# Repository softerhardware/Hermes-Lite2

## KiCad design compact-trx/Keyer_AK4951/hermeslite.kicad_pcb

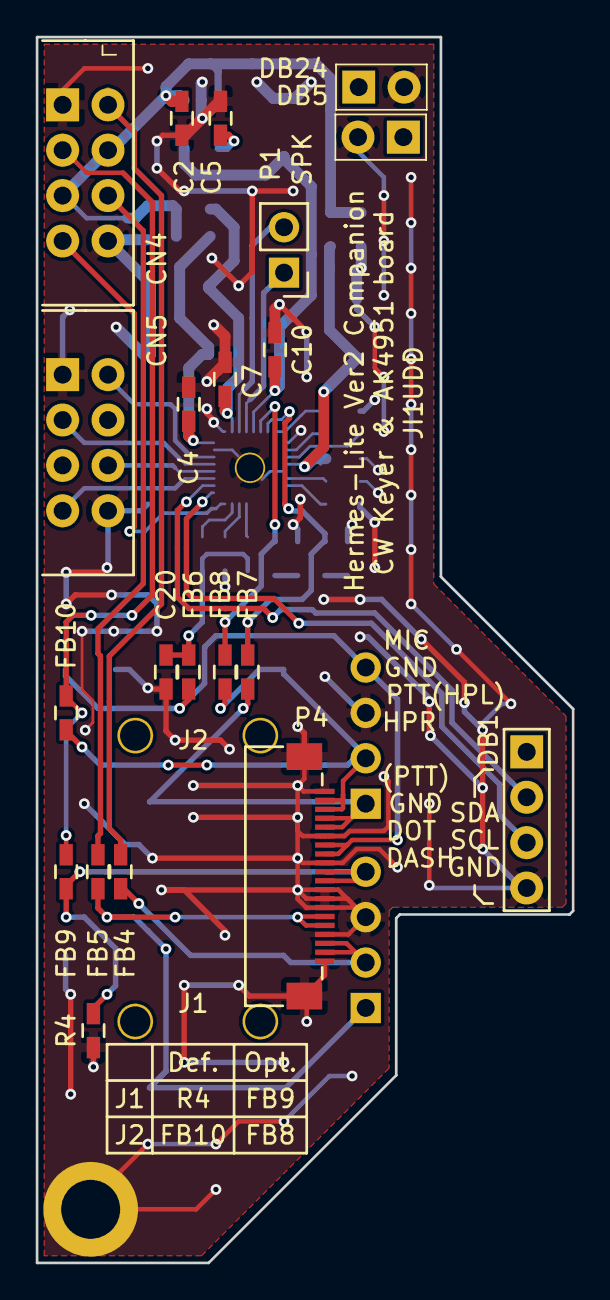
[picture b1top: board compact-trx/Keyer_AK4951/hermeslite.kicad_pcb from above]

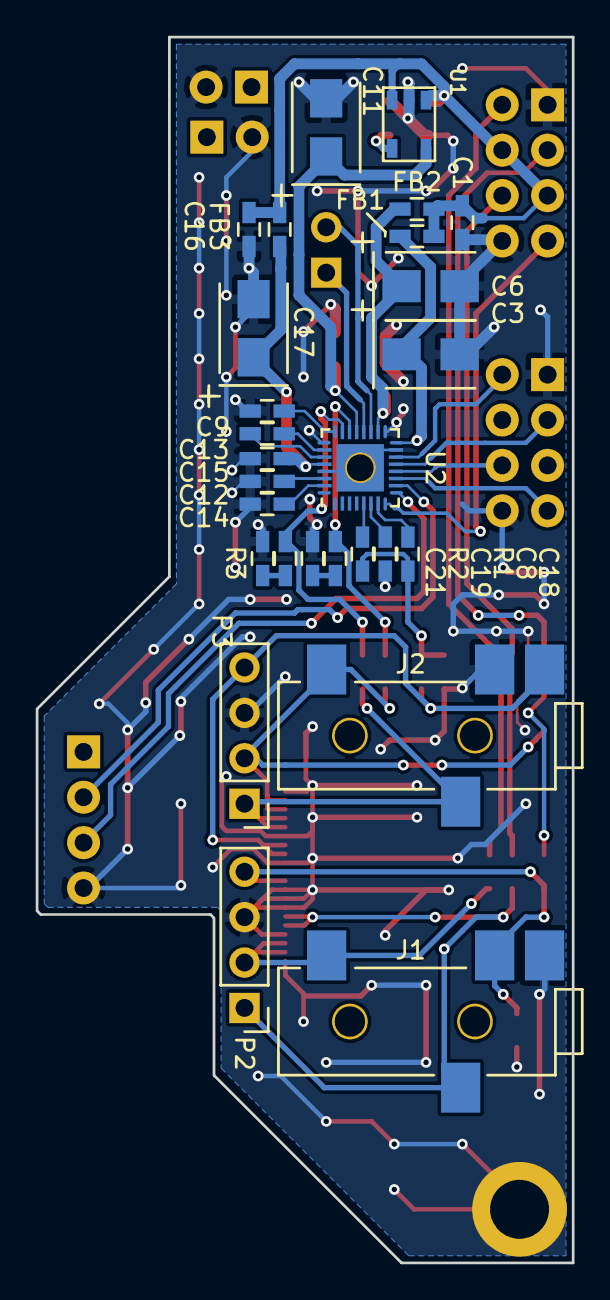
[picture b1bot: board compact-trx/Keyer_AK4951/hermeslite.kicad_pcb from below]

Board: 4 copper layers, 30.0 x 68.6 mm, 49 parts (27 on the bottom side), 38 nets.

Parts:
C1, C4, C5, C7, C10, C15, C16: 0.1u; C_0603_HandSoldering
C2, C8, C18: 1u; C_0603_HandSoldering
C3, C6, C11, C17: 10u; TantalC_SizeB_EIA-3528_Wave
C9, C12, C13, C14: 2.2u; C_0603_HandSoldering
C19, C21: 0.22u; C_0603_HandSoldering
C20: DNI; C_0603_HandSoldering
CN4, CN5: IO8; IO
DB1: RFD4d; 4x1
DB5, DB24: RFD2b; 2x1
FB1, FB2, FB3, FB4, FB5, FB6, FB7, FB8, FB9, FB10: FB; C_0603_HandSoldering
J1, J2: SJ-43514-SMT
MH2: DNI; m3
P1: CONN_01X02; Pin_Header_Straight_1x02_Pitch2.54mm
P2, P3: CONN_01X04; Pin_Header_Straight_1x04_Pitch2.54mm
P4: FFC 20pin; FFC_Kyocera_20pin
R1: 2.2k; C_0603_HandSoldering
R2, R3: 33; C_0603_HandSoldering
R4: 0; C_0603_HandSoldering
U1: TPS730; SOT23
U2: AK4951AEN; QFN-32-1EP_4x4mm_Pitch0.4mm_Handsoldering

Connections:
+3V3: C1.1, C2.1, C16.1, CN4.4, CN4.5, FB1.2, FB2.2, FB3.1, U1.1, U1.3
/AudioCodec/BCK: CN5.2, U2.14
/AudioCodec/DIN: CN5.7, U2.11
/AudioCodec/DOUT: CN5.6, U2.12
/AudioCodec/LRCK: CN5.3, U2.13
/AudioCodec/P2-1: FB5.2, J1.3, P2.1, P4.15, P4.16
/AudioCodec/P2-2: FB4.2, J1.2, P2.2, P4.18, P4.19
/AudioCodec/P2-4: FB9.1, J1.4, P2.4, P4.10, P4.11, R4.2
/AudioCodec/P3-1: FB7.2, J2.3, P3.1, P4.4, P4.5
/AudioCodec/P3-2: FB8.1, FB10.1, J2.2, P3.2, P4.2, P4.3
/AudioCodec/P3-4: FB6.2, J2.1, P3.4, P4.7, P4.8
/AudioCodec/PDN: CN4.7, U2.8
/AudioCodec/SCL: DB1.3, U2.9
/AudioCodec/SDA: DB1.2, U2.10
/AudioCodec/~DASH: CN4.6, FB5.1
/AudioCodec/~DOT: CN4.2, FB4.1
/AudioCodec/~PTT: CN4.3, FB9.2, FB10.2
GND: C1.2, C2.2, C3.2, C4.2, C5.2, C6.2, C7.2, C8.1, C9.2, C10.2, C11.2, C12.2, C14.2, C15.1, C16.2, C17.2, C20.2, CN4.1, CN4.8, CN5.1, CN5.8, DB1.4, DB5.2, DB24.2, J1.1, J2.4, MH2.1, P2.3, P3.3, P4.1, P4.6, P4.9, P4.12, P4.13, P4.14, P4.17, P4.20, P4.21, P4.22, R2.2, R3.2, R4.1, U1.2, U2.15, U2.17, U2.25, U2.29, U2.33
unnamed: C3.1, C4.1, FB1.1, U2.16
unnamed: C5.1, U1.4
unnamed: C6.1, C7.1, FB2.1, U2.18
unnamed: C8.2, U2.6
unnamed: C9.1, U2.24
unnamed: C10.1, C11.1, U1.5, U2.21
unnamed: C12.1, U2.30
unnamed: C13.1, U2.27
unnamed: C13.2, U2.26
unnamed: C14.1, U2.31
unnamed: C15.2, C17.1, FB3.2, U2.28
unnamed: C18.1, U2.7
unnamed: C18.2, C20.1, FB6.1, R1.1
unnamed: C19.1, FB8.2, U2.22
unnamed: C19.2, R2.1
unnamed: C21.1, FB7.1, U2.23
unnamed: C21.2, R3.1
unnamed: P1.1, U2.20
unnamed: P1.2, U2.19
unnamed: R1.2, U2.5

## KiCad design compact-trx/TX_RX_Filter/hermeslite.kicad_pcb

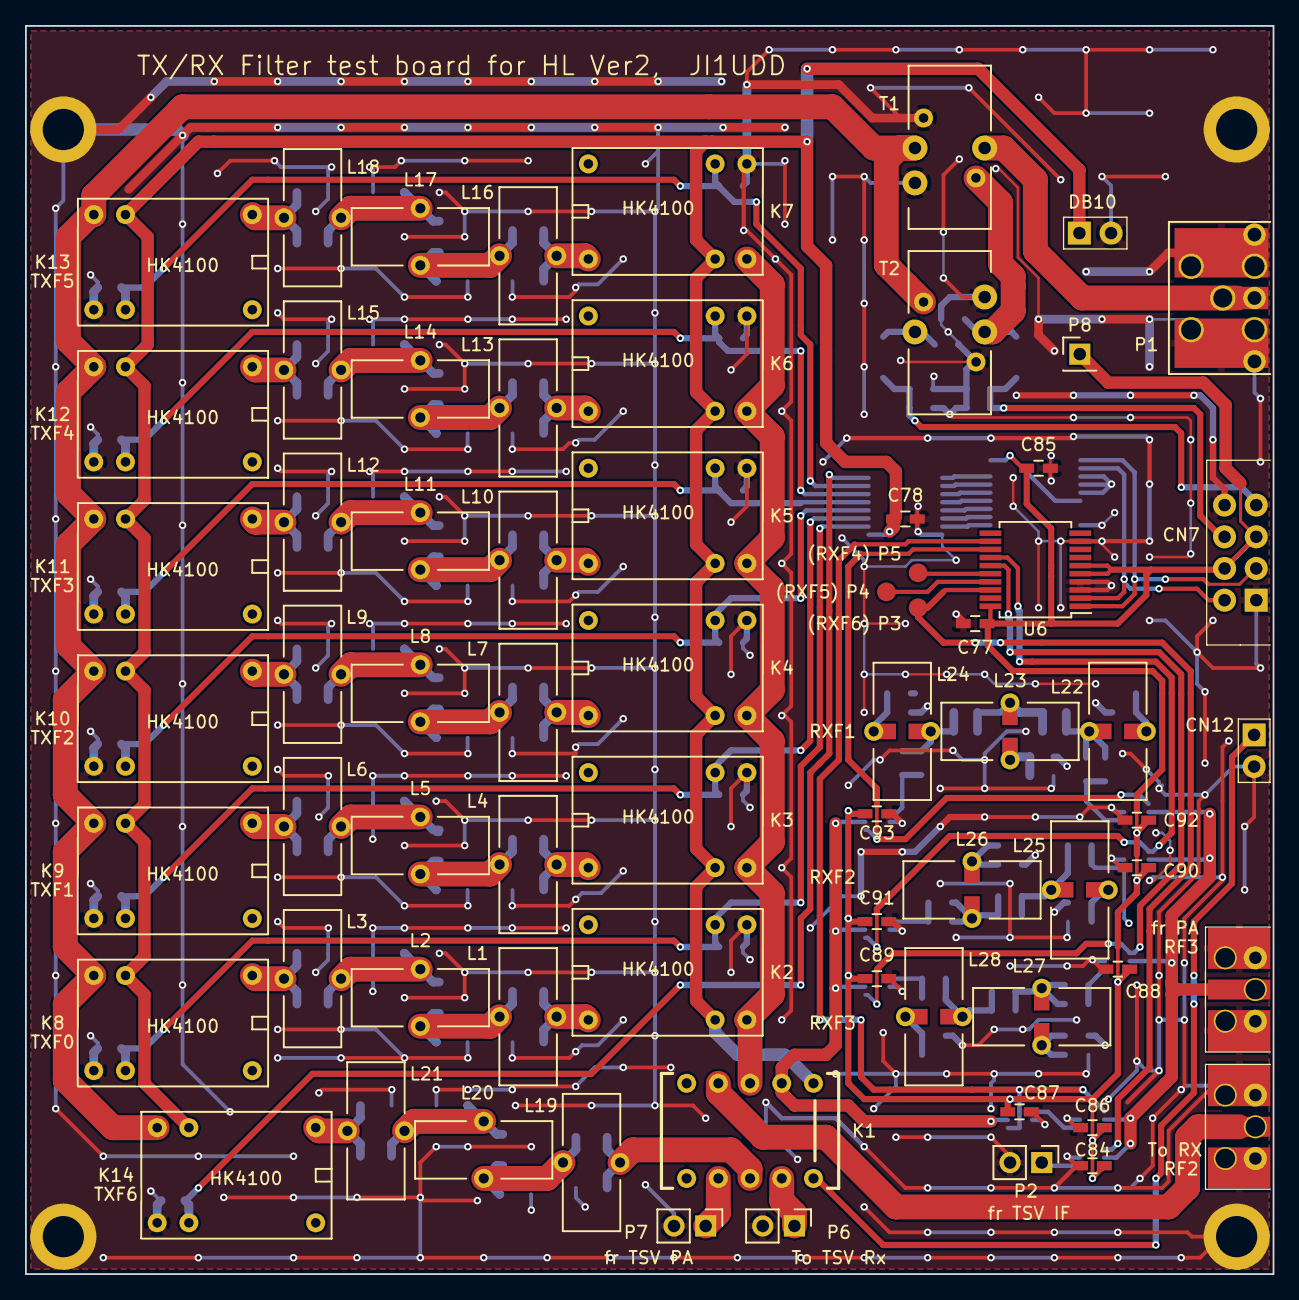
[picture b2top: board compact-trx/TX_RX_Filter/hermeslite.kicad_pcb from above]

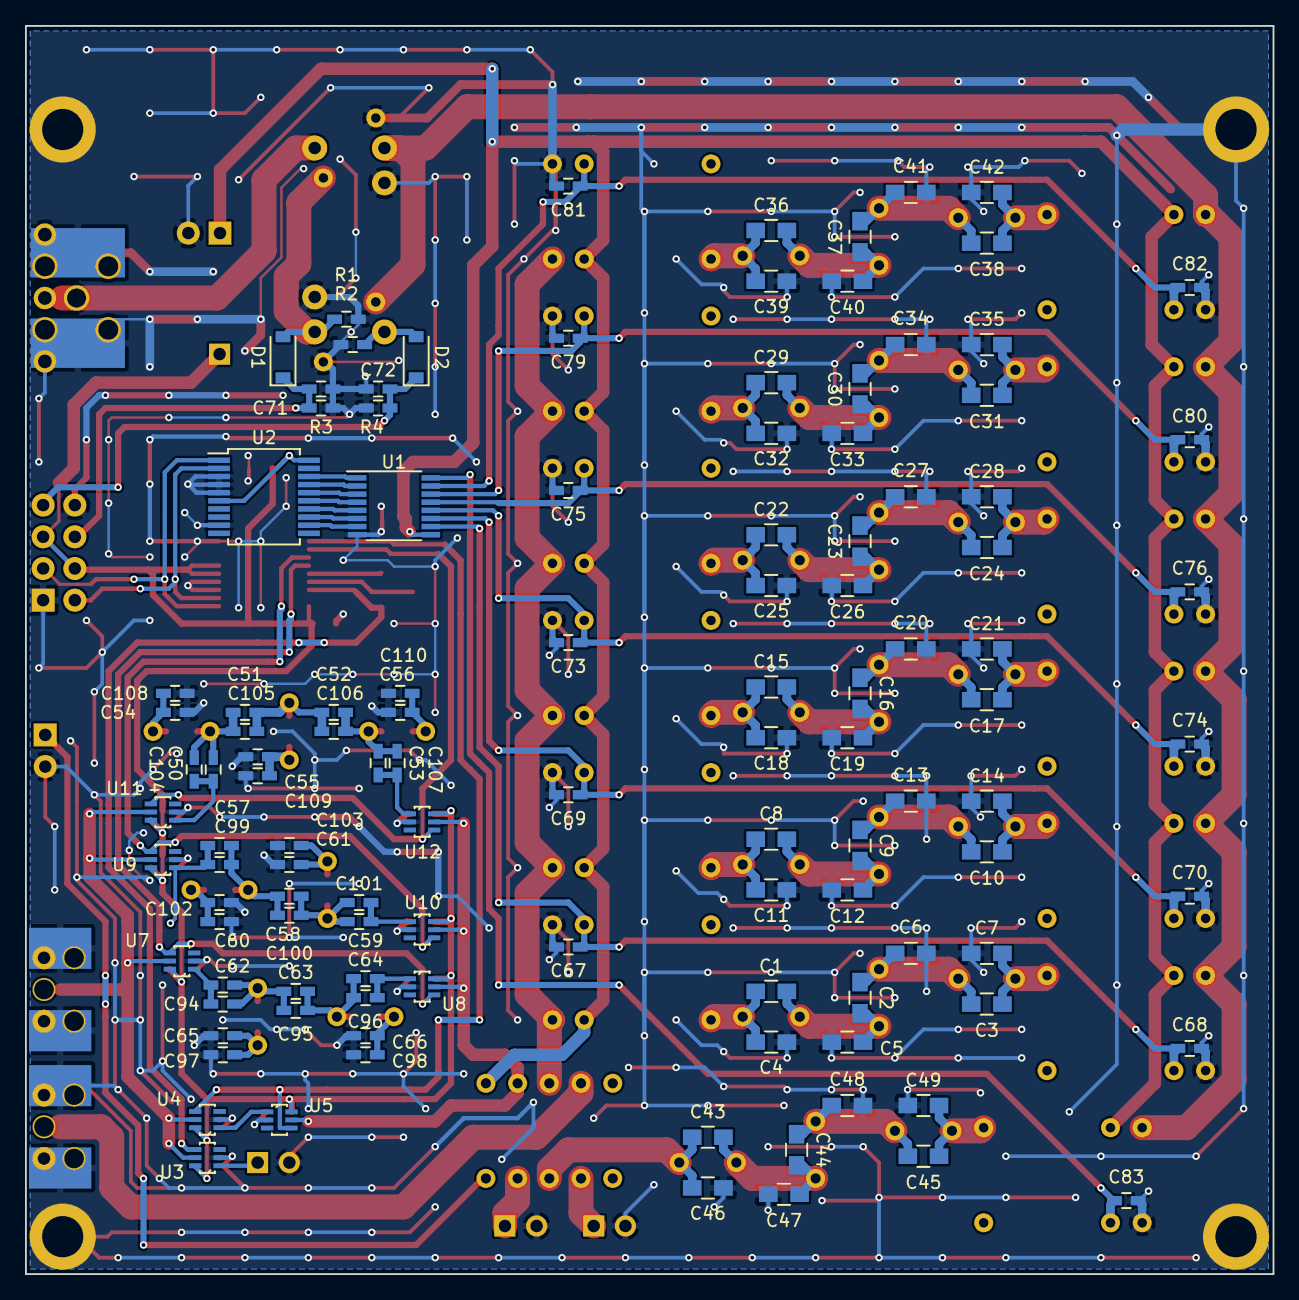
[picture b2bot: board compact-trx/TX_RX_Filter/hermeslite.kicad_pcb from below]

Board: 4 copper layers, 99.9 x 100.0 mm, 189 parts (115 on the bottom side), 89 nets.

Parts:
C1, C2, C3, C8, C9, C10, C17, C28, C29, C30, C31, C36, C37, C38, C43, C44, C45, C46, C47, C48, C49: DNI; C_0805_HandSoldering
C4, C7: 820p; C_0805_HandSoldering
C5, C6: 2200p; C_0805_HandSoldering
C11, C14: 470pF; C_0805_HandSoldering
C12, C13: 1200pF; C_0805_HandSoldering
C15: 100pf; C_0805_HandSoldering
C16: 300pf; C_0805_HandSoldering
C18: 360pF; C_0805_HandSoldering
C19: 680pF; C_0805_HandSoldering
C20: 270pF; C_0805_HandSoldering
C21: 240pF; C_0805_HandSoldering
C22: 43pF; C_0805_HandSoldering
C23, C27: 130pF; C_0805_HandSoldering
C24: 0R Res; C_0805_HandSoldering
C25: 180pF; C_0805_HandSoldering
C26: 300pF; C_0805_HandSoldering
C32, C35: 82pF; C_0805_HandSoldering
C33, C34: 220pF; C_0805_HandSoldering
C39, C42: 100p; C_0805_HandSoldering
C40, C41: 180p; C_0805_HandSoldering
C50, C51, C52, C53, C57, C58, C59, C62, C63, C64, C94, C95, C96, C99, C100, C101, C104, C105, C106, C107: DNI; C_0603_HandSoldering
C54, C55, C56, C60, C61, C65, C66, C97, C98, C102, C103, C108, C109, C110: 10p; C_0603_HandSoldering
C67, C68, C69, C70, C73, C74, C75, C76, C79, C80, C81, C82, C83: 10n; C_0603_HandSoldering
C71, C72, C77, C78, C84, C85, C86, C87, C88, C89, C90, C91, C92, C93: 100n; C_0603_HandSoldering
CN7: IO8; IO
CN12: RFD2b; 2x1
D1, D2: 1N5711; D_SOD-123
DB10: RFD2b; 2x1
K1: RELAY_EA2; Relay_EA2
K2, K3, K4, K5, K6, K7, K8, K9, K10, K11, K12, K13, K14: HK4100
L1, L3: 4.442u; T37_SL
L2: 5.608u; T37_SL
L4, L6: 2.434uH; T37_SL
L5: 3.012uH; T37_SL
L7: 1.156uH; T37_SL
L8: 676nH; T37_SL
L9: 576nH; T37_SL
L10: 642.5nH; T37_SL
L11: 455nH; T37_SL
L12, L19, L20, L21: DNI; T37_SL
L13, L15: 444nH; T37_SL
L14: 561nH; T37_SL
L16, L18: 330nH; T37_SL
L17: 270nH; T37_SL
L22, L23, L24, L25, L26, L27, L28: 330nH; T37_SL_SMD
MH1, MH2, MH3, MH4: DNI; m3
P1: SMA; rfconnectorB-1
P2, P6, P7: CONN_01X02; Pin_Header_Straight_1x02_Pitch2.54mm
P3, P4, P5: TST; Measurement_Point_Round-SMD-Pad_Small
P8: TST; Pin_Header_Straight_1x01_Pitch2.54mm
R1, R2: 50.1; C_0603_HandSoldering
R3, R4: 100k; C_0603_HandSoldering
RF2: SMA; SMAEDGE_TH
RF3: BNC; SMAEDGE_TH
T1, T2: PWR_TRANS_FS; FR-Power-Xfmr_FS
U1: TPL7407LPW; TSSOP-16_4.4x5mm_Pitch0.65mm
U2, U6: MCP23008-SS; SSOP-20_5.3x7.2mm_Pitch0.65mm
U3, U4, U5, U7, U8, U9, U10, U11, U12: PE4259

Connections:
+3V3: C77.1, C84.1, C85.1, C86.1, C87.1, C88.1, C89.1, C90.1, C91.1, C92.1, C93.1, CN7.4, CN7.5, P8.1, U2.6, U2.20, U3.6, U4.6, U5.6, U6.5, U6.6, U6.20, U7.6, U8.6, U9.6, U10.6, U11.6, U12.6
+12V: C78.1, DB10.1, K1.1, K2.5, K3.5, K4.5, K5.5, K6.5, K7.5, K8.5, K9.5, K10.5, K11.5, K12.5, K13.5, K14.5, U1.9
/TXF0: C67.1, C68.1, K2.2, K8.2, U1.10
/TXF1: C69.1, C70.1, K3.2, K9.2, U1.11
/TXF2: C73.1, C74.1, K4.2, K10.2, U1.12
/TXF3: C75.1, C76.1, K5.2, K11.2, U1.13
/TXF4: C79.1, C80.1, K6.2, K12.2, U1.14
/TXF5: C81.1, C82.1, K7.2, K13.2, U1.15
/TXF6: C83.1, K14.2, U1.16
/rx-filter/RX-FILTER-IN: K1.2, U5.5, U8.5, U10.5, U12.5
/tx-filter/AIN1: C71.2, CN7.6, D1.1, R3.1
/tx-filter/AIN2: C72.1, CN7.7, D2.1, R4.2
GND: C4.2, C5.2, C6.2, C7.2, C11.2, C12.2, C13.2, C14.2, C18.2, C19.2, C20.2, C21.2, C25.2, C26.2, C27.2, C28.2, C32.2, C33.2, C34.2, C35.2, C39.2, C40.2, C41.2, C42.2, C46.2, C47.2, C48.2, C49.2, C54.2, C55.2, C56.2, C60.2, C61.2, C65.2, C66.2, C67.2, C68.2, C69.2, C70.2, C71.1, C72.2, C73.2, C74.2, C75.2, C76.2, C77.2, C78.2, C79.2, C80.2, C81.2, C82.2, C83.2, C84.2, C85.2, C86.2, C87.2, C88.2, C89.2, C90.2, C91.2, C92.2, C93.2, C97.2, C98.2, C102.2, C103.2, C108.2, C109.2, C110.2, CN7.1, CN7.8, CN12.2, DB10.2, K2.1, K3.1, K4.1, K5.1, K6.1, K7.1, K8.1, K9.1, K10.1, K11.1, K12.1, K13.1, K14.1, MH1.1, MH2.1, MH3.1, MH4.1, P1.2, P2.2, P6.2, P7.2, R1.2, R2.1, R3.2, R4.1, RF2.2, RF3.2, T1.3, T1.5, T2.3, T2.5, U1.8, U2.3, U2.4, U2.5, U2.9, U3.2, U4.2, U5.2, U6.3, U6.4, U6.9, U7.2, U8.2, U9.2, U10.2, U11.2, U12.2
unnamed: C1.1, C2.2, C5.1, L1.2, L2.1
unnamed: C1.2, C4.1, K2.4, L1.1
unnamed: C2.1, C3.2, C6.1, L2.2, L3.1
unnamed: C3.1, C7.1, K8.4, L3.2
unnamed: C10.1, C14.1, K9.4, L6.2
unnamed: C9.1, C10.2, C13.1, L5.2, L6.1
unnamed: C8.2, C11.1, K3.4, L4.1
unnamed: C8.1, C9.2, C12.1, L4.2, L5.1
unnamed: C15.1, C16.2, C19.1, L7.2, L8.1
unnamed: C15.2, C18.1, K4.4, L7.1
unnamed: C16.1, C17.2, C20.1, L8.2, L9.1
unnamed: C17.1, C21.1, K10.4, L9.2
unnamed: C22.1, C23.2, C26.1, L10.2, L11.1
unnamed: C22.2, C25.1, K5.4, L10.1
unnamed: C23.1, C24.2, C27.1, L11.2, L12.1
unnamed: C24.1, C28.1, K11.4, L12.2
unnamed: C29.1, C30.2, C33.1, L13.2, L14.1
unnamed: C29.2, C32.1, K6.4, L13.1
unnamed: C30.1, C31.2, C34.1, L14.2, L15.1
unnamed: C31.1, C35.1, K12.4, L15.2
unnamed: C36.1, C37.2, C40.1, L16.2, L17.1
unnamed: C36.2, C39.1, K7.4, L16.1
unnamed: C37.1, C38.2, C41.1, L17.2, L18.1
unnamed: C38.1, C42.1, K13.4, L18.2
unnamed: C43.1, C44.2, C47.1, L19.2, L20.1
unnamed: C44.1, C45.2, C48.1, L20.2, L21.1
unnamed: C45.1, C49.1, K14.4, L21.2
unnamed: C57.2, C99.2, U9.1
unnamed: C62.1, C63.2, C94.1, C95.2, L27.1
unnamed: C62.2, C94.2, U7.1
unnamed: C63.1, C64.2, C95.1, C96.2, L28.1
unnamed: C64.1, C96.1, U8.1
unnamed: C65.1, C97.1, L27.2
unnamed: C66.1, C98.1, L28.2
unnamed: C58.1, C59.2, C100.1, C101.2, L26.1
unnamed: C57.1, C58.2, C99.1, C100.2, L25.1
unnamed: C59.1, C101.1, U10.1
unnamed: C60.1, C102.1, L25.2
unnamed: C61.1, C103.1, L26.2
unnamed: C50.1, C51.2, C104.1, C105.2, L22.1
unnamed: C50.2, C104.2, U11.1
unnamed: C51.1, C52.2, C105.1, C106.2, L23.1
unnamed: C52.1, C53.2, C106.1, C107.2, L24.1
unnamed: C53.1, C107.1, U12.1
unnamed: C54.1, C108.1, L22.2
unnamed: C55.1, C109.1, L23.2
unnamed: C56.1, C110.1, L24.2
unnamed: CN12.1, K1.10
unnamed: D1.2, R1.1, T1.4, T2.1
unnamed: D2.2, R2.2, T2.2
unnamed: K1.4, RF2.1
unnamed: K1.7, P7.1
unnamed: K1.9, P6.1
unnamed: K8.6, K9.6, K10.6, K11.6, K12.6, K13.6, K14.6, T1.1, T2.4
unnamed: P1.1, T1.2
unnamed: P2.1, U3.1
unnamed: P4.1, U6.17
unnamed: P5.1, U6.16
unnamed: RF3.1, U3.5, U4.5, U7.5, U9.5, U11.5
unnamed: U1.1, U2.18
unnamed: U1.2, U2.17
unnamed: U1.3, U2.16
unnamed: U1.4, U2.15
unnamed: U1.5, U2.14
unnamed: U1.6, U2.13
unnamed: U1.7, U2.12
unnamed: U4.1, U5.1
RXF0: U4.4, U5.4, U6.12
RXF1: U6.13, U11.4, U12.4
RXF2: U6.14, U9.4, U10.4
RXF3: U6.15, U7.4, U8.4
RXF6: P3.1, U3.4, U6.18
SCL: CN7.3, U2.1, U6.1
SDA: CN7.2, U2.2, U6.2
TSV-FILTER: C43.2, C46.1, K1.8, L19.1
TX-FILTER-IN: K1.3, K2.6, K3.6, K4.6, K5.6, K6.6, K7.6

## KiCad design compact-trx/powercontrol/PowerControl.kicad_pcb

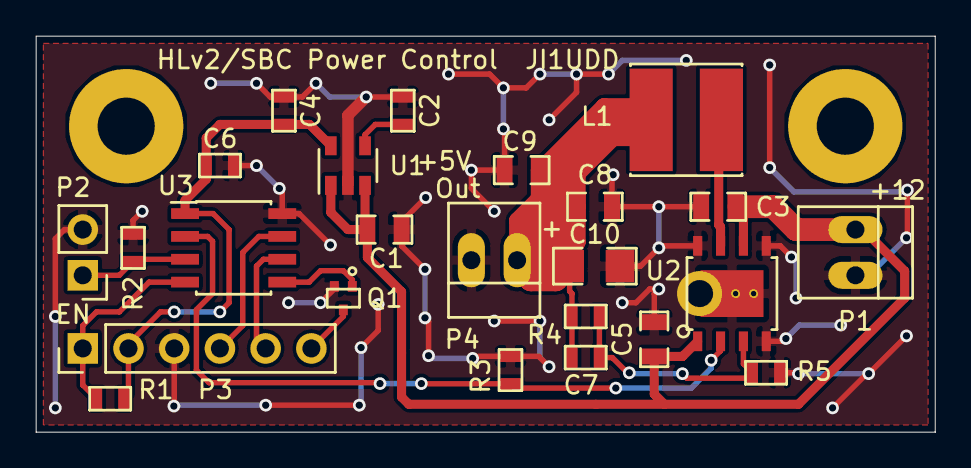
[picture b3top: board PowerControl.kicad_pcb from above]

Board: 2 copper layers, 49.9 x 22.0 mm, 26 parts (0 on the bottom side), 14 nets.

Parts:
C1: 1uF/25V; SMD-0805
C2: 0.01uF; SMD-0603
C3: 10uF/25V; SMD-0805
C4: 2.2uF/10V; SMD-0603
C5: 4.7uF/25V; SMD-0805
C6: 0.1uF; SMD-0603
C7: 4.7nF; SMD-0603
C8, C9: 22uF/6.3V; SMD-0805
C10: 100uF/6.3V; SMD-1206
L1: 3.3uH; GENERICPSL
MH: VAL**; MH
MH#2: VAL**; MH
P1, P4: CONN_01X02; PINHEAD1-2
P2: CONN_01X02; Pin_Header_Straight_1x02_Pitch2.54mm
P3: CONN_01X06; Pin_Header_Straight_1x06_Pitch2.54mm
Q1: DTC144E; SOT416
R1, R2, R3, R5: 10k; SMD-0603
R4: 53.6k; SMD-0603
U1: TAR5SB33; SOT-23-5
U2: ST1S10
U3: PIC12F1822-E/SN; SOIC-8_3.9x4.9mm_Pitch1.27mm

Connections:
GND: C1.2, C2.2, C3.2, C4.2, C5.2, C6.1, C8.2, C9.2, C10.2, P1.2, P2.2, P3.3, P4.2, Q1.2, R2.2, R3.2, R5.2, U1.2, U2.4, U2.5, U2.8, U2.9, U3.8
unnamed: C1.1, C3.1, C5.1, P1.1, U1.1, U1.3, U2.1, U2.6
unnamed: C2.1, U1.4
unnamed: C4.1, C6.2, P3.2, R1.1, U1.5, U3.1
unnamed: C7.2, R4.2, R5.1, U2.3
unnamed: C7.1, C8.1, C9.1, C10.1, L1.2, P4.1, R4.1
unnamed: L1.1, U2.7
unnamed: P2.1, R2.1, U3.3
unnamed: P3.1, R1.2, U3.4
unnamed: P3.4, U3.7
unnamed: P3.5, U3.6
unnamed: P3.6, Q1.3
unnamed: Q1.1, U3.5
unnamed: R3.1, U2.2, U3.2
